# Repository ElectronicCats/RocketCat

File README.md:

# RocketCat: Kit of Water Rocket WiFi

Fuente: Ein wahres Probiertes und Pracktisches geschriebenes Feuerbuch <br>
Autor: Franz Helm

Si tu eres un fanatico de los cohetes y deseas experimentar con electronica, WiFi y cohetes de agua, RocketCat es un kit open source para niños, adultos y todo fan que desea aprender de esta tecnologia. ¡Ciencia en acción!

### Construye y lanza un cohete
Construye tu propio cohete con solo una botella, electronica, agua y una bomba. ¡Mira cómo el cohete se eleva muy alto mientras bombeas aire hacia él! Alimentado por agua y presión de aire mientras observas todos los cambios de aceleracion, orientacion y altura en tu smartphone o computadora.

### Ciencia y aprendizaje divertidos
El Kit RocketCat es perfecto para el estudiante o el entusiasta de la ciencia. Se incluye todo lo que necesita para construir su propio cohete de agua mientras aprende sobre la tecnología.

### Todo para construir tu cohete
El kit Rocket contiene:

- 1 Botella de plástico
- 4 Aletas (una para el repuesto)
- 1 Soporte para aletas
- 1 Tapón
- 1 Conector para tapón 
- 1 Conector para bomba 
- 1 Tubo de extensión de plástico, 
- 1 Tarjeta electronica para montaje
- Modulo WiFi ESP8266
- Sensor de presion y altura BMP180
- GY-87 sensor de aceleracion, magnetrometro y giroscopio
- Instrucciones detalladas

El nombre esta inspirado en el trabajo e ilustraciones de [Franz Helm](https://en.wikipedia.org/wiki/Franz_Helm) y su **Rocket Cat**

## TODO

- Wiki con instrucciones
- Mejora de web de monitoreo
- Soporte para ESP32 and BLE

## LICENSE

Electronic Cats invierte tiempo y recursos al proporcionar este diseño de fuente abierta, por favor ayude a Electronic Cats y hardware de código abierto comprando productos de Electronic Cats.

Diseñado por Electronic Cats.

Firmware lanzado bajo una licencia de GNU AGPL v3.0. Vea el archivo LICENCIA para más información.

Hardware lanzado bajo una licencia de hardware Open CERN v1.2. Consulte el archivo LICENSE_HARDWARE para obtener más información.

Electronic Cats es una marca registrada, no la use si vende estos PCB.

7 Dic 2017

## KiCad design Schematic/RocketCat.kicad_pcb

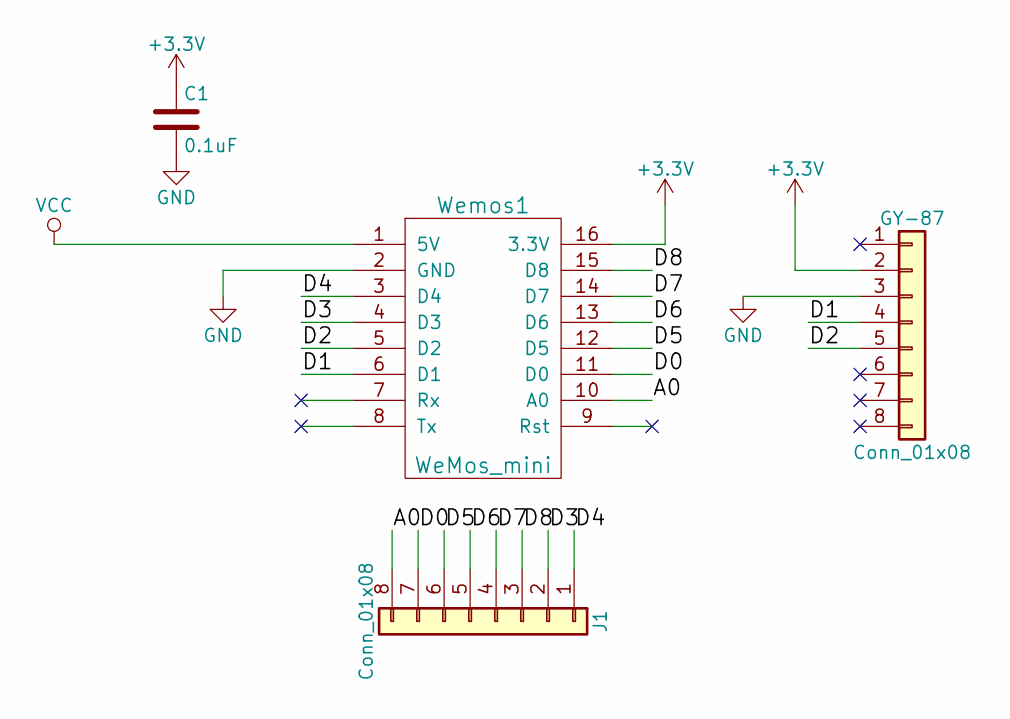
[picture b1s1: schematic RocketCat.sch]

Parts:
C1: 0.1uF
GY-87: Conn_01x08; Socket_Strip_Straight_1x08_Pitch2.54mm
J1: Conn_01x08; Socket_Strip_Straight_1x08_Pitch2.54mm
Wemos1: WeMos_mini; wemos-d1-mini-connectors-only

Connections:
+3V3: C1.1, GY-87.2, Wemos1.16 (3.3V)
/A0: J1.8, Wemos1.10 (A0)
/D0: J1.7, Wemos1.11 (D0)
/D1: GY-87.4, Wemos1.6 (D1)
/D2: GY-87.5, Wemos1.5 (D2)
/D3: J1.2, Wemos1.4 (D3)
/D4: J1.1, Wemos1.3 (D4)
/D5: J1.6, Wemos1.12 (D5)
/D6: J1.5, Wemos1.13 (D6)
/D7: J1.4, Wemos1.14 (D7)
/D8: J1.3, Wemos1.15 (D8)
GND: C1.2, GY-87.3, Wemos1.2 (GND)
VCC: Wemos1.1 (5V)

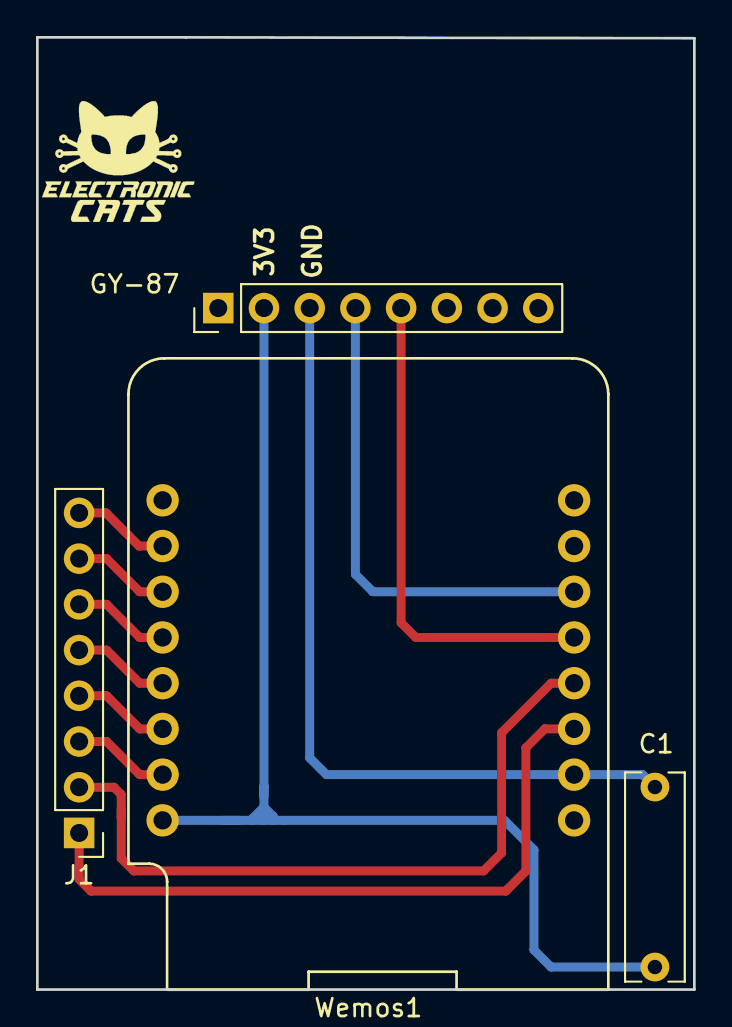
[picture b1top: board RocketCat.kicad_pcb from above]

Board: 2 copper layers, 36.5 x 52.9 mm, 4 parts (0 on the bottom side), 12 nets.

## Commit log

2017-12-08 Agregado Sketch Arduino
2017-12-08 Agregado sensor BMP180
2017-12-08 Agregado MPU6050
    :v papi sabas
2017-12-11 Agregado HMC5883
    Pequeño porblema con "Y" y "Z" de magsensor
2017-12-12 Magnetometro funcionando
2017-12-19 Incluido el web y los datos.
    Falta mostrar datos en web.
2017-12-22 Incluyendo el refresh
    Refresh
2017-12-22 Agregando cuerpo html
    formato normal
2017-12-22 Agregando Presion, Temperatura y Altitud.
2017-12-22 Agregando Giroscopio y aceleracion.
    incluye con los datos denuevo del giroscopio y aceleracion.
2017-12-22 Agregando magsensor
    al igual que x y z esta los datos y agregados a html
2017-12-22 Un plus, Agregando imagen
    aun falta guardarlo en el ESP8266
2017-12-22 Agregando detalles finales.
2017-12-23 Actualizacion de README
2017-12-23 Create LICENSE
2017-12-23 Create LICENSE_HARDWARE
2018-01-08 Agregado esquematico
2018-01-08 Listo
    borrando pequeños detalles
2018-01-09 Esquematico de WeMos PCB
    Aun falta poner los pines
2018-01-09 Net del esquematico
    Agregado WeMos para simulacion
2018-01-10 Esquematico de Wemos
    Denuevo por error de no visualizacion
2018-01-10 Todods lo datos del esquematico y pcb
2018-01-10 Agregado Bateria y gy 87
    en lo de la pbc me falta un pista, lo podrias poner pof favor xd
2018-01-12 PCB Lista
    Checar si no tengo nada mal
2018-01-15 Pcb aun no lista. v.0.1
    Se redujo el espacio, para no desperdiciarlo.
    Arreglo de pistas de 0.25mm a 0.3mm
    Espacio definido para el GY87
2018-01-18 fix size and tracks remove MCP charger
2018-01-18 Añadido logo de EC
2018-02-16 Actualizado Webserver
    Se disminuyo el refresh a 0.1 seg, para obtener datos mas rapido.
